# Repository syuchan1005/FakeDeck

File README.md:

# Fakedeck
Using raspberry pi pico as a stream deck

## Avaiable devices

|Mk2|Plus|
|:--:|:--:|
|||

## How to create : StreamDeck Mk.2
### Parts
- Raspberry Pi Pico
- ILI9488 TFT with Touch: [AliExpress](https://www.aliexpress.com/item/32985467436.html)
> [!IMPORTANT]
> Make sure to select "touch screen"
- Solder, wire, etc.
- 3D printers for creating a case - [Top](./assets/Mk2/Case%20-%20Top.stl), [Bottom](./assets/Mk2/Case%20-%20Bottom.stl)
- M3 x 6mm screw *4

### Wire

> [!NOTE]
> LCD uses 90 mA. 
> In the example, the back of the LCD is shaved and soldered to hold the pico in place.

### Build
1. Setup [PlatformIO IDE](https://platformio.org/platformio-ide)
2. Clone and open this project
3. Change environment to `pico_deckMk2`
4. Build .uf2 file!

## How to create : StreamDeck+
### Parts
- Raspberry Pi Pico W
- SSD1963 TFT with Touch: [AliExpress](https://www.aliexpress.com/item/1005006305412643.html)
> [!IMPORTANT]
> Make sure to select "resistive touch"
- Rotary encoder with switch (PEC12R-4220F-S0024) * 4: [Digikey](https://www.digikey.jp/short/jrrh2j7r), [Monotaro](https://www.monotaro.com/p/3483/7593/)
- Stripboard(approx. 120 x 90 (mm)) or Order PCB
- 3D printers for creating a case - [Top](./assets/Plus/Case%20-%20Top.stl), [Bottom body](./assets/Plus/Case%20-%20Bottom%20body.stl), [Bottom base](./assets/Plus/Case%20-%20Bottom%20base.stl), [Bottom bridge](./assets/Plus/Case%20-%20Bottom%20bridge.stl)
- M3 x 6mm screw *4
- Resistors: 47Ω, 120Ω, 220Ω, 470Ω, 1kΩ

> These resistors are used in the switch's ladder circuit. Any other value is acceptable as long as it is a constant multiple of the specified resistance. If using resistors other than these, modify `SW_PATTERNS` in [Encoder.hpp](./src/input/Encoder.hpp).

### Wire

|Front|Back|
|:--:|:--:|
|||

> These are for the old PCB.

### projects

#### pico_avrisp_wifi
> not used
Write to avr microcontroller (attiny2313) using Raspberry Pi Pico W via WiFi

This project access WiFi AP. You should copy `config.sample.ini` to `config.ini`, and change values to your Wifi settings.

> [!NOTE]
> In my enviroment, [avrdude](https://github.com/avrdudes/avrdude) can not communicate with Raspberry Pi Pico via usb serial. So, It write to avr microcontroller via WiFi.

> [!IMPORTANT]
> In my environment, avrdude 6.3(PlatformIO embedded version) can not write via WiFi. Please update to **^7.3**. (You can replace files in `tool-avrdude` package)

#### avr
> not used
Get the four rotary encoder with push switch values via SPI.

### Build
#### Custom PCB
This project includes the [kicad project](./assets/Plus/kicad).

> [!WARNING]
> It includes gerber files, but they are for the old PCB.

#### Hardware
Solder the rotary encoders with reference to the [kicad project](./assets/Plus/kicad), making sure that the Screen display area is correct before soldering the rotary encoders.

#### Software
1. Setup [PlatformIO IDE](https://platformio.org/platformio-ide)
2. Clone and open this project
3. Change environment to `pico_deckPlus`, build and upload.

## Tips
- [HID Explorer](https://nondebug.github.io/webhid-explorer/) is an easy HID testing tool using WebHID
- Reboot device and enter bootsel mode: Send `[02, FF]` to the output report
- Reboot device: Send `[02, FE]` to the output report

## Reference
- [ESP8266AVRISP](https://github.com/esp8266/Arduino/tree/19b7a29720a6f2c95d06e2ea4baa335dcf32e68f/libraries/ESP8266AVRISP)
- [avr-usi-spi](https://github.com/tessel/avr-usi-spi/blob/77ce496d6bc404684158e619695c2fb7bc76815a/spi_via_usi_driver.c)

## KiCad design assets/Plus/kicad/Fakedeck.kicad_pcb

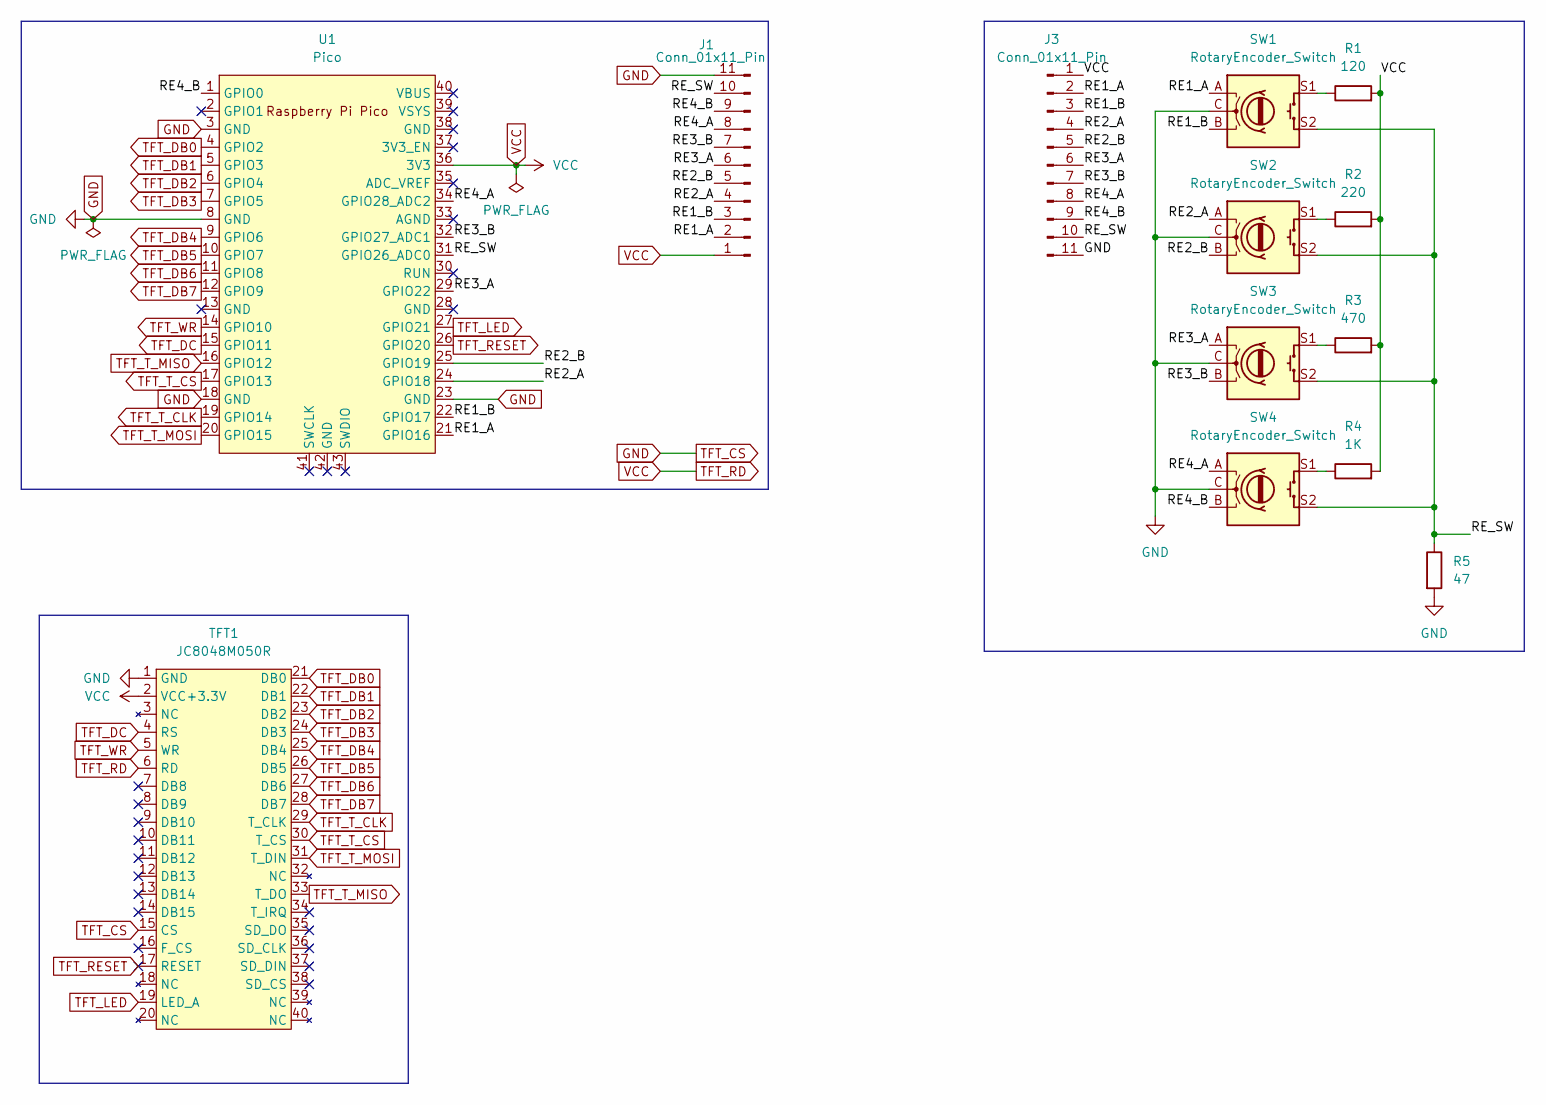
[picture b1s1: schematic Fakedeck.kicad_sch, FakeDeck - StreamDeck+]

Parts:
J1, J3: Conn_01x11_Pin; PinHeader_Castellated_1x11_P2.54mm_Vertical
R1: 120; R_Axial_DIN0207_L6.3mm_D2.5mm_P7.62mm_Horizontal
R2: 220; R_Axial_DIN0207_L6.3mm_D2.5mm_P7.62mm_Horizontal
R3: 470; R_Axial_DIN0207_L6.3mm_D2.5mm_P7.62mm_Horizontal
R4: 1K; R_Axial_DIN0207_L6.3mm_D2.5mm_P7.62mm_Horizontal
R5: 47; R_Axial_DIN0207_L6.3mm_D2.5mm_P7.62mm_Horizontal
SW1, SW2, SW3, SW4: RotaryEncoder_Switch; 3D_RotaryEncoder_Bourns_Vertical_PEC12R-3x17F-Sxxxx
TFT1: JC8048M050R; JC8048M050R_PinHeader
U1: Pico; RPi_Pico_SMD_TH

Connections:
/RE1_A: J1.2, J3.2, SW1.A, U1.21 (GPIO16)
/RE1_B: J1.3, J3.3, SW1.B, U1.22 (GPIO17)
/RE2_A: J1.4, J3.4, SW2.A, U1.24 (GPIO18)
/RE2_B: J1.5, J3.5, SW2.B, U1.25 (GPIO19)
/RE3_A: J1.6, J3.6, SW3.A, U1.29 (GPIO22)
/RE3_B: J1.7, J3.7, SW3.B, U1.32 (GPIO27_ADC1)
/RE4_A: J1.8, J3.8, SW4.A, U1.34 (GPIO28_ADC2)
/RE4_B: J1.9, J3.9, SW4.B, U1.1 (GPIO0)
/RE_SW: J1.10, J3.10, R5.1, SW1.S2, SW2.S2, SW3.S2, SW4.S2, U1.31 (GPIO26_ADC0)
GND: J1.11, J3.11, R5.2, SW1.C, SW2.C, SW3.C, SW4.C, TFT1.1 (GND), TFT1.15 (CS), U1.3 (GND), U1.8 (GND), U1.18 (GND), U1.23 (GND)
unnamed: R1.1, SW1.S1
unnamed: R2.1, SW2.S1
unnamed: R3.1, SW3.S1
unnamed: R4.1, SW4.S1
TFT_DB0: TFT1.21 (DB0), U1.4 (GPIO2)
TFT_DB1: TFT1.22 (DB1), U1.5 (GPIO3)
TFT_DB2: TFT1.23 (DB2), U1.6 (GPIO4)
TFT_DB3: TFT1.24 (DB3), U1.7 (GPIO5)
TFT_DB4: TFT1.25 (DB4), U1.9 (GPIO6)
TFT_DB5: TFT1.26 (DB5), U1.10 (GPIO7)
TFT_DB6: TFT1.27 (DB6), U1.11 (GPIO8)
TFT_DB7: TFT1.28 (DB7), U1.12 (GPIO9)
TFT_DC: TFT1.4 (RS), U1.15 (GPIO11)
TFT_LED: TFT1.19 (LED_A), U1.27 (GPIO21)
TFT_RD: J1.1, J3.1, R1.2, R2.2, R3.2, R4.2, TFT1.2 (VCC+3.3V), TFT1.6 (RD), U1.36 (3V3)
TFT_RESET: TFT1.17 (RESET), U1.26 (GPIO20)
TFT_T_CLK: TFT1.29 (T_CLK), U1.19 (GPIO14)
TFT_T_CS: TFT1.30 (T_CS), U1.17 (GPIO13)
TFT_T_MISO: TFT1.33 (T_DO), U1.16 (GPIO12)
TFT_T_MOSI: TFT1.31 (T_DIN), U1.20 (GPIO15)
TFT_WR: TFT1.5 (WR), U1.14 (GPIO10)

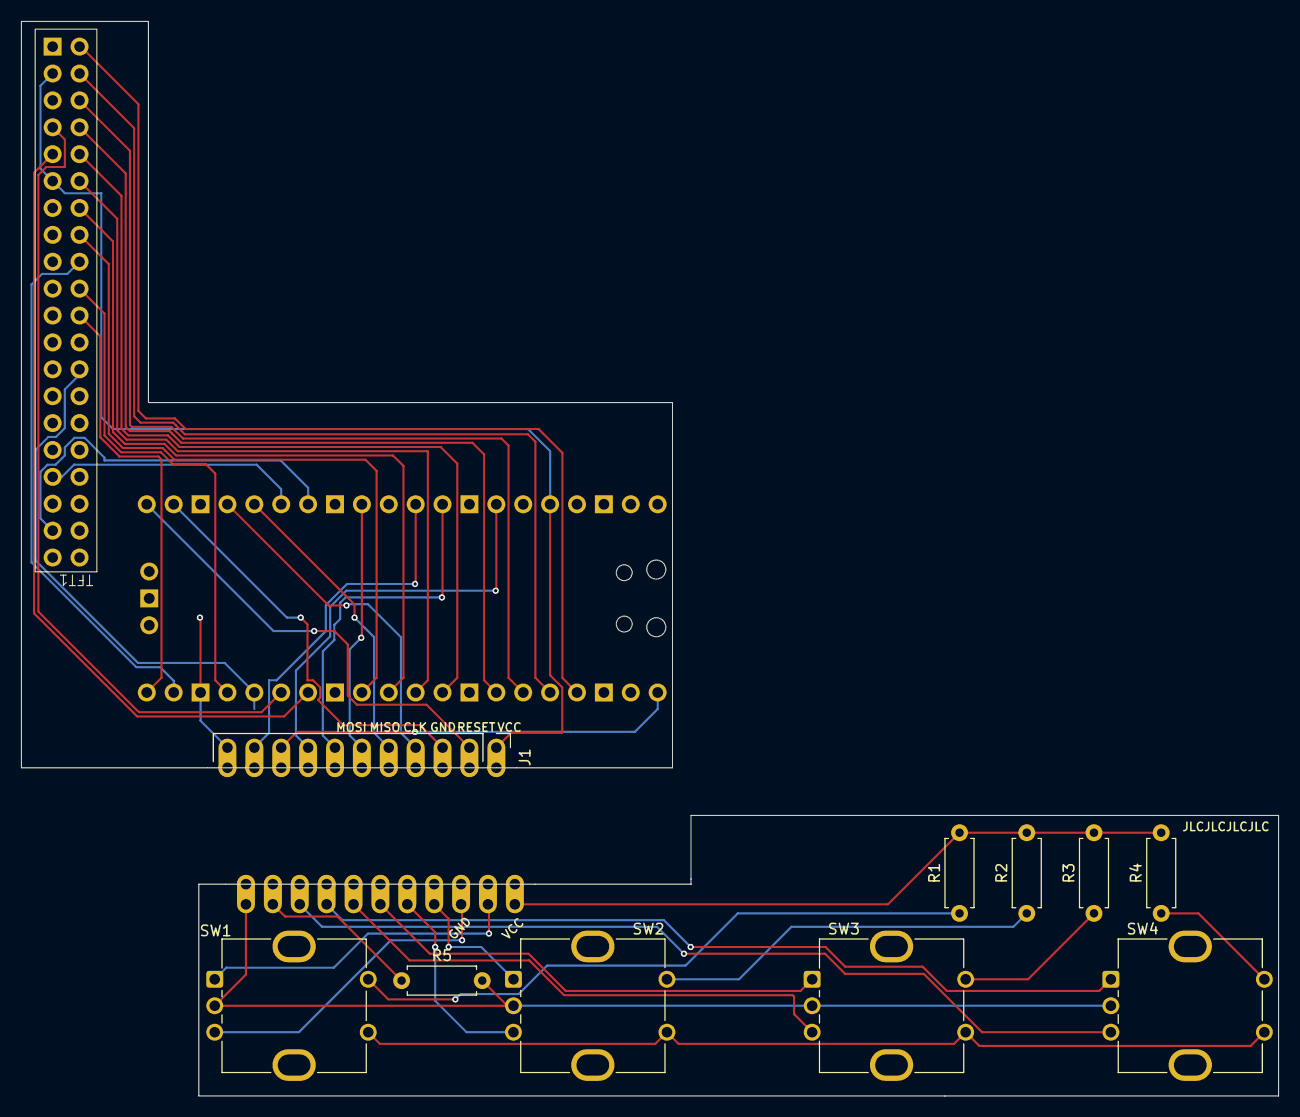
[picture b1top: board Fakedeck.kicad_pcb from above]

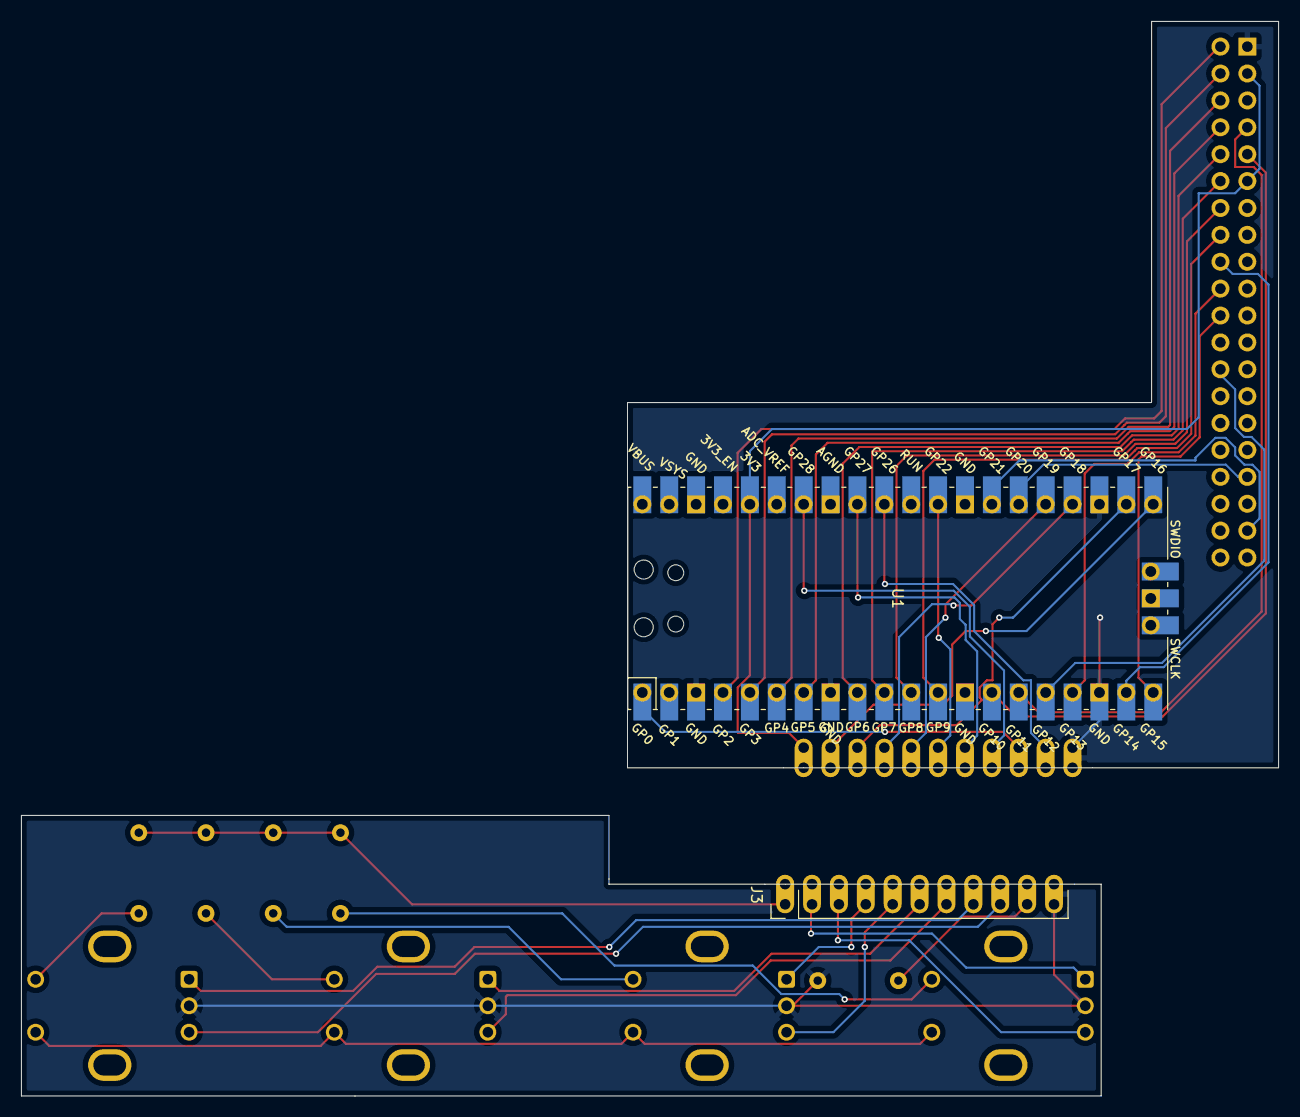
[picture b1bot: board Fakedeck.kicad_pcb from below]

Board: 2 copper layers, 118.8 x 101.5 mm, 13 parts (2 on the bottom side), 31 nets.

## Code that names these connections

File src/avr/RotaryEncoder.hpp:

#include <avr/io.h>

#define RE1_PR_DIR_REG DDRA
#define RE1_PR_OUT_REG PORTA
#define RE1_PR_DATA_REG PINA
#define RE1_PR_DIR_REG_S DDRD
#define RE1_PR_OUT_REG_S PORTD
#define RE1_PR_DATA_REG_S PIND
#define RE1_A PA1
#define RE1_B PA0
#define RE1_S PD2

#define RE2_PR_DIR_REG DDRD
#define RE2_PR_OUT_REG PORTD
#define RE2_PR_DATA_REG PIND
#define RE2_A PD3
#define RE2_B PD4
#define RE2_S PD5

#define RE3_PR_DIR_REG DDRB
#define RE3_PR_OUT_REG PORTB
#define RE3_PR_DATA_REG PINB
#define RE3_A PB4
#define RE3_B PB3
#define RE3_S PB2

#define RE4_PR_DIR_REG DDRB
#define RE4_PR_OUT_REG PORTB
#define RE4_PR_DATA_REG PINB
#define RE4_PR_DIR_REG_S DDRD
#define RE4_PR_OUT_REG_S PORTD
#define RE4_PR_DATA_REG_S PIND
#define RE4_A PB1
#define RE4_B PB0
#define RE4_S PD6

void initRotaryEncoders()
{
    // config rotary encoder pins, input_pullup
    RE1_PR_DIR_REG &= ~(1 << RE1_A) | ~(1 << RE1_B);
    RE1_PR_OUT_REG |= (1 << RE1_A) | (1 << RE1_B);
    RE1_PR_DIR_REG_S &= ~(1 << RE1_S);
    RE1_PR_OUT_REG_S |= (1 << RE1_S);

    RE2_PR_DIR_REG &= ~(1 << RE2_A) | ~(1 << RE2_B) | ~(1 << RE2_S);
    RE2_PR_OUT_REG |= (1 << RE2_A) | (1 << RE2_B) | (1 << RE2_S);

    RE3_PR_DIR_REG &= ~(1 << RE3_A) | ~(1 << RE3_B) | ~(1 << RE3_S);
    RE3_PR_OUT_REG |= (1 << RE3_A) | (1 << RE3_B) | (1 << RE3_S);

    RE4_PR_DIR_REG &= ~(1 << RE4_A) | ~(1 << RE4_B);
    RE4_PR_OUT_REG |= (1 << RE4_A) | (1 << RE4_B);
    RE4_PR_DIR_REG_S &= ~(1 << RE4_S);
    RE4_PR_OUT_REG_S |= (1 << RE4_S);
}

void createRotaryEncoderData(
    uint8_t index,
    uint16_t rePinDataReg, uint8_t aPin, uint8_t bPin,
    uint16_t reSPinDataReg, uint8_t sPin,
    uint16_t *data, uint16_t *oldData, uint16_t *sendData)
{
    uint8_t offset = index * 2;
    // read pin data
    if (rePinDataReg & (1 << aPin))
        *data |= 1 << (0 + offset);
    if (rePinDataReg & (1 << bPin))
        *data |= 1 << (1 + offset);
    if (~reSPinDataReg & (1 << sPin))
        *sendData |= 1 << (8 + index);

    // old A and old B are both high
    if ((*oldData & (3 << offset)) == (3U << offset))
    {
        if ((*data & (3 << offset)) == (1U << offset))
        {
            // A is high and B is low - Clockwise
            *sendData |= 1 << offset;
        }
        else if ((*data & (3 << offset)) == (2U << offset))
        {
            // A is low and B is high - Counter-clockwise
            *sendData |= 1 << (1 + offset);
        }
    }
}

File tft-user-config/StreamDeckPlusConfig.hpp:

/**
 * TFT configuration for the StreamDeckPlus
 */

#if !defined(USER_SETUP_LOADED)
#define USER_SETUP_LOADED

#define TFT_PARALLEL_8_BIT

#define SSD1963_800_DRIVER

#define TFT_RGB_ORDER TFT_RGB

#define TFT_ROTATION 3

// #define TFT_CS // to GND
// #define TFT_RD // to 3V3
#define TFT_DC 11
#define TFT_RST 20
#define TFT_WR 10

// PIO requires these to be sequentially increasing
#define TFT_D0 2
#define TFT_D1 3
#define TFT_D2 4
#define TFT_D3 5
#define TFT_D4 6
#define TFT_D5 7
#define TFT_D6 8
#define TFT_D7 9

#define TFT_LED 21

#define LOAD_GLCD
#define LOAD_FONT2
#define LOAD_FONT4
#define LOAD_FONT6
#define LOAD_FONT7
#define LOAD_FONT8
#define LOAD_GFXFF
#define SMOOTH_FONT

#define USE_ORIGINAL_TOUCH
#define TFT_MISO2 12
#define TFT_MOSI2 15
#define TFT_SCLK2 14
#define TOUCH_CS2 13
#define TOUCH_X p.y, 3700, 250
#define TOUCH_Y p.x, 450, 3600
#define TOUCH_THRESHOLD 400
#endif // USER_SETUP_LOADED

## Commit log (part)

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2024-02-27 Init commit
2024-02-27 Add code
2024-03-02 Fix build: version and serial are defined twice
2024-03-02 Add encoder
2024-03-02 Add Encoders class
2024-04-19 Extract output report id
2024-04-27 Add original v2 profile
2024-04-27 Add LCD support
2024-04-29 Support PIO_SPI
2024-04-29 Remove unused file and Rename files
2024-05-01 Add TFT_LED for backlight
2024-05-01 Add image and case model
2024-05-01 Add debug feature to reboot into bootsel mode
2024-05-01 Support brightness feature
2024-05-01 Add debug feature to reboot
2024-05-01 Reduce key down report
2024-05-02 Remove unnecessary serial
2024-05-02 Remove unnecessary defines
2024-05-02 Fix readme
2024-05-05 Split usb_descriptors.hpp to deck_config.hpp
2024-05-05 Avoid white screen flashing
2024-05-05 Remove delay call
2024-05-05 Move backlight functions to LCD
2024-05-05 Remove unnecessary argument
2024-05-05 Remove unnecessary Serial.print
2024-05-06 Use core1 as TFT LCD processes
2024-05-12 Add USE_ORIGINAL_TOUCH define
2024-05-15 Add button border
2024-06-06 Upgrade earlephilhower/arduino-pico to 3.9.0
2024-07-07 Replace Jpeg decoder library to JPEGDEC
2024-07-21 Add pico-avrisp-wifi project
2024-07-21 Add avr project
2024-07-21 Implement rotary encoder logics
2024-07-21 Revert replace jpeg decoder due to memory
2024-07-21 Split tft config from platformio.ini
2024-07-21 Add pico_deckPlus
2024-07-24 Adjust queue
2024-07-29 Change the queue data from image data to HID packet
2024-07-29 Add tft calibrate data define
2024-07-29 Extract key button point calculations
2024-07-29 Add draw_touch_image
2024-07-29 Change pin assigning
2024-07-29 Add LCD event handler
2024-08-01 Add DEBUG_SPI flag and validate bits
2024-08-01 Add encoder logics
2024-08-01 Move LCD class namespace to Input::Display
2024-08-06 Add kicad files for plus
2024-08-06 Add case files for plus
2024-08-06 Add plus image
2024-08-06 Update README and pio envs
2024-08-06 Fix typo
2024-08-06 Add pillars to support the screen
2024-08-16 Add overclock setting
2024-08-16 Add TOUCH_THRESHOLD option
2024-11-19 Update libraries
2024-11-19 Remove bodmer/TJpg_Decoder
2024-11-19 Add workaround for include build flag
2026-03-02 Add CLAUDE.md
